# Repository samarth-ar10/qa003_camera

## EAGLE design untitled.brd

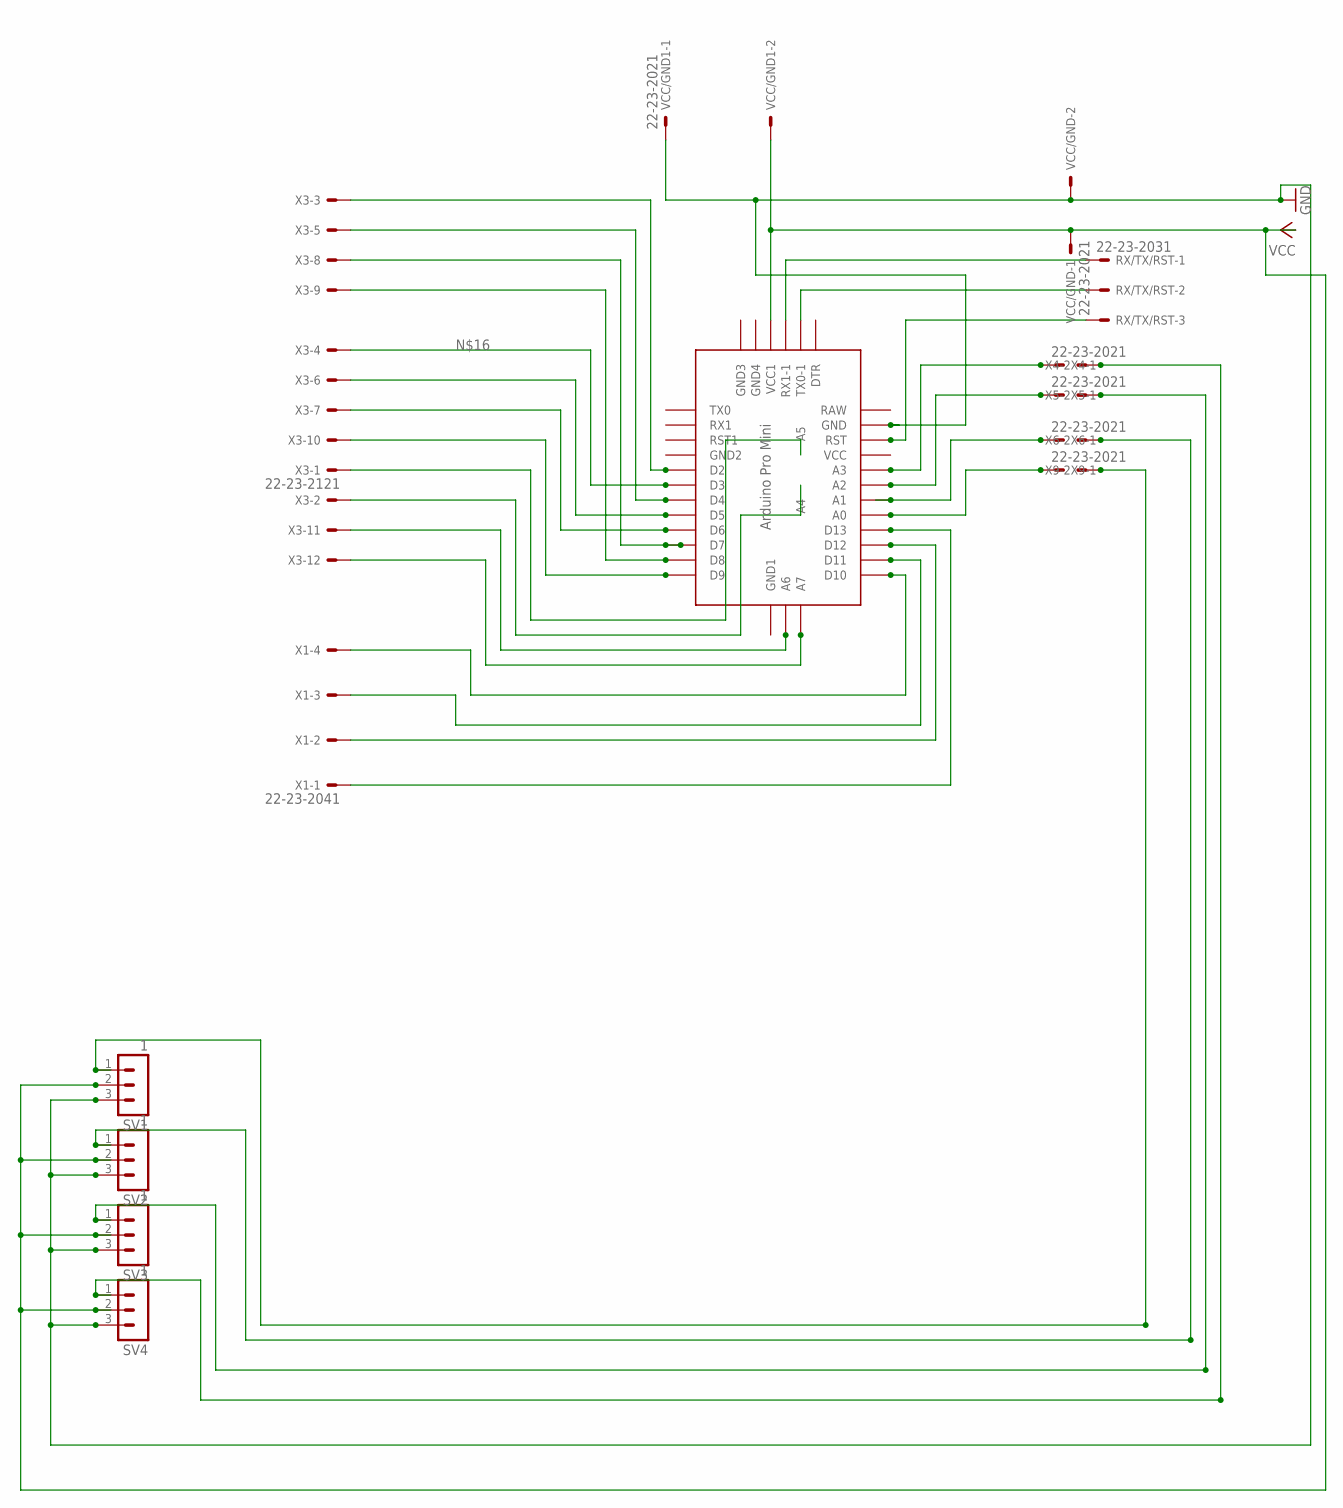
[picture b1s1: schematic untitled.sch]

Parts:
RX/TX/RST: 22-23-2031
SV1, SV2, SV3, SV4: 1; MA03-1
U$1: ABK-PRO-MINI
VCC/GND, VCC/GND1: 22-23-2021
X1: 22-23-2041
X3: 22-23-2121
X4, X5, X6, X9: 22-23-2021

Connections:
GND: SV1.3, SV2.3, SV3.3, SV4.3, U$1.GND, VCC/GND.2, VCC/GND1.1
unnamed: RX/TX/RST.2, U$1.TX0-1
unnamed: U$1.A3, X4.1
unnamed: U$1.D10, X1.4
unnamed: U$1.A2, X5.1
unnamed: RX/TX/RST.3, U$1.RST
unnamed: SV4.1, X4.2
unnamed: SV3.1, X5.2
unnamed: SV2.1, X6.2
unnamed: SV1.1, X9.2
unnamed: U$1.D4, X3.5
unnamed: U$1.D7, X3.8
unnamed: U$1.D8, X3.9
unnamed: U$1.D2, X3.3
unnamed: U$1.D3, X3.4
unnamed: U$1.D5, X3.6
unnamed: U$1.D6, X3.7
unnamed: U$1.D9, X3.10
unnamed: U$1.A5, X3.1
unnamed: U$1.A4, X3.2
unnamed: U$1.A6, X3.11
unnamed: U$1.A7, X3.12
unnamed: U$1.A1, X6.1
unnamed: RX/TX/RST.1, U$1.RX1-1
unnamed: U$1.D11, X1.3
unnamed: U$1.D12, X1.2
unnamed: U$1.D13, X1.1
unnamed: U$1.A0, X9.1
VCC: SV1.2, SV2.2, SV3.2, SV4.2, U$1.VCC1, VCC/GND.1, VCC/GND1.2

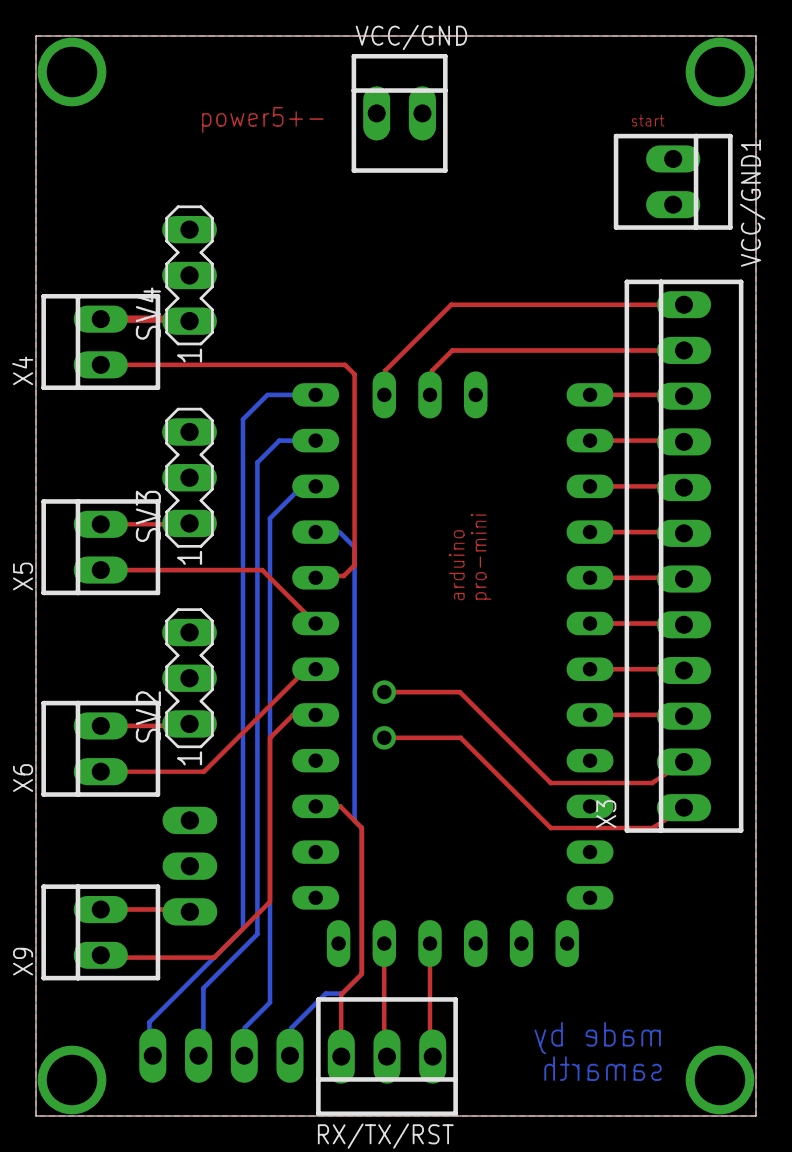
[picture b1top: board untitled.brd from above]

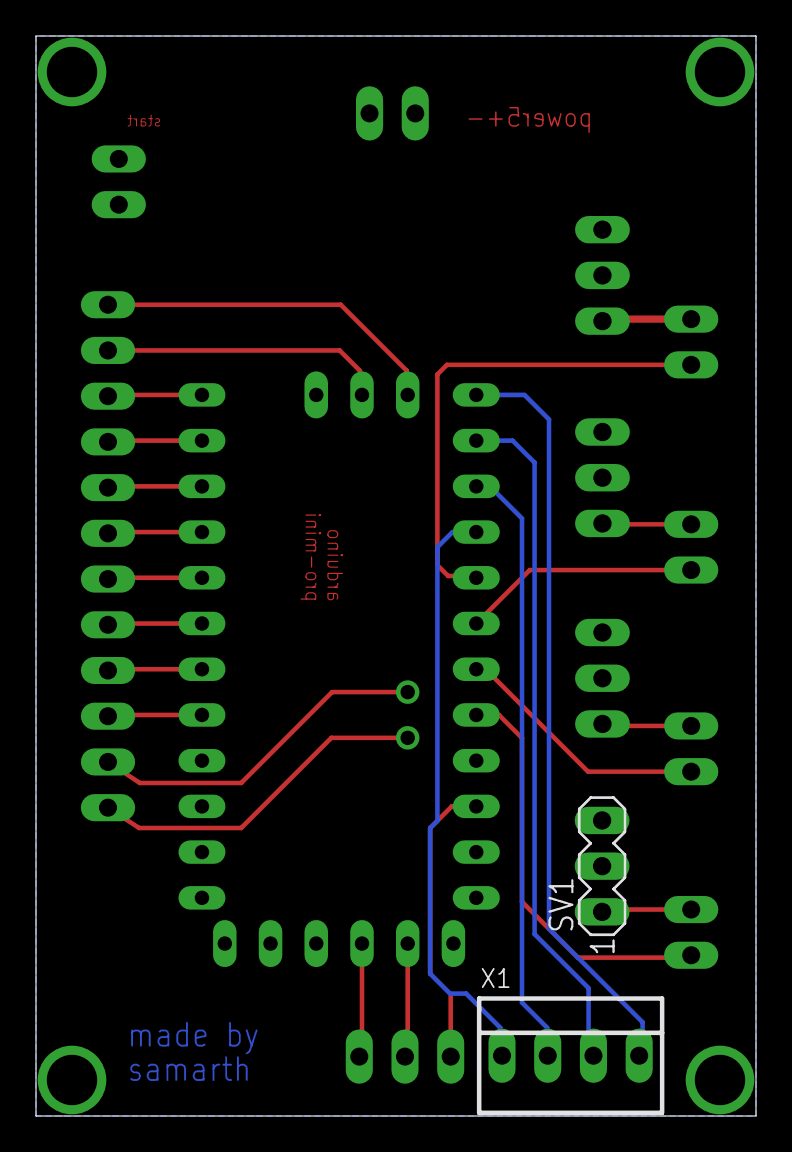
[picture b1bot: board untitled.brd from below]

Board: 2 copper layers, 40.0 x 60.0 mm, 14 parts (2 on the bottom side), 29 nets.

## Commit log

2020-03-01 pushing files to GitHub
2020-03-15 Adding Images
2020-11-09 Uploading stl and correcting name
